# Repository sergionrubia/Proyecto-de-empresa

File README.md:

# sergio
Este va a ser mi repositorio donde voy a guardar todo aquello relacionado con las practicas que estoy haciendo durante mi proyecto de empresa.

Durante este proyecto voy a aprender el funcionamiento del EcoTherm con cada una de sus diferentes partes:
	
	1) Medida Analógica.
	2) Contador (Pulsos).
	3) Medición de temperatura.

De momento en los proyectos subidos a fecha 8 de abril de 2022 están subidos las practicas de de cada una de las partes del EcoTherm y además la primera prática que hice con arduino que consiste en el encendido de varios led con una secuencia programada.

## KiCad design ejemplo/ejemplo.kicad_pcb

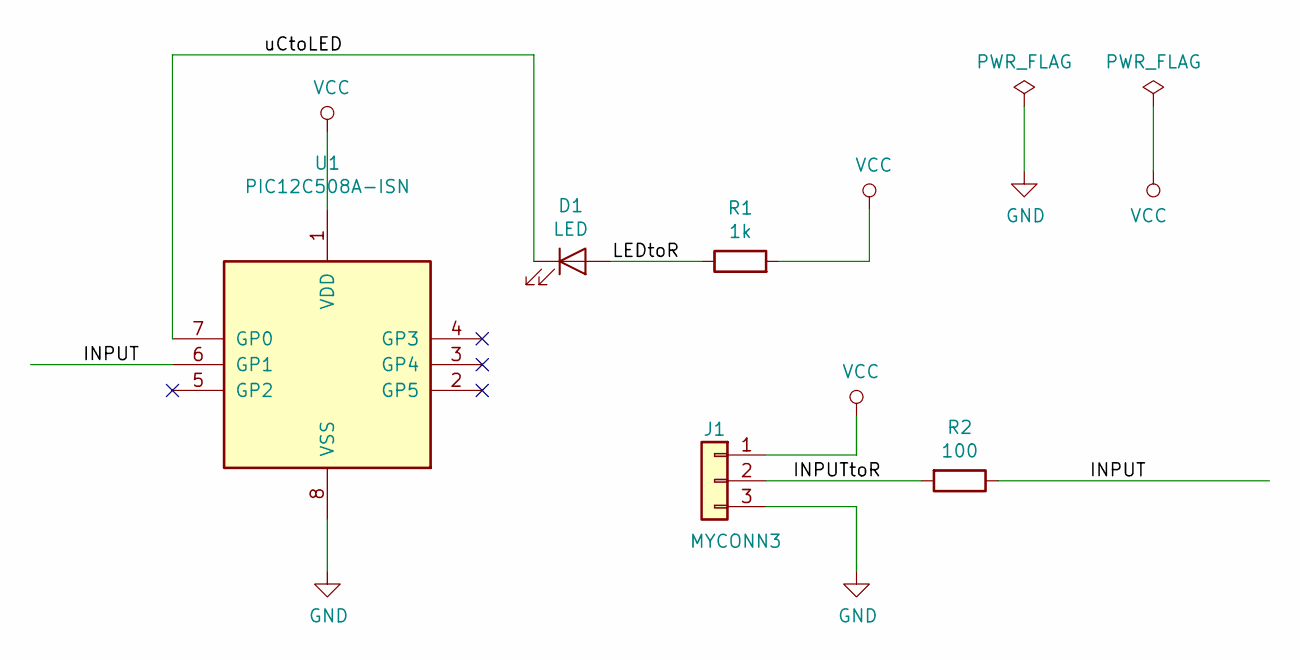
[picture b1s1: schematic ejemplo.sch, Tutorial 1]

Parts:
D1: LED; LED_D5.0mm
J1: MYCONN3; Banana_Jack_3Pin
R1: 1k; R_Axial_DIN0204_L3.6mm_D1.6mm_P1.90mm_Vertical
R2: 100; R_Axial_DIN0204_L3.6mm_D1.6mm_P1.90mm_Vertical
U1: PIC12C508A-ISN; DIP-8_W7.62mm

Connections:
/INPUT: R2.1, U1.6 (GP1)
/INPUTtoR: J1.2, R2.2
/LEDtoR: D1.2 (A), R1.1
/uCtoLED: D1.1 (K), U1.7 (GP0)
GND: J1.3, U1.8 (VSS)
VCC: J1.1, R1.2, U1.1 (VDD)

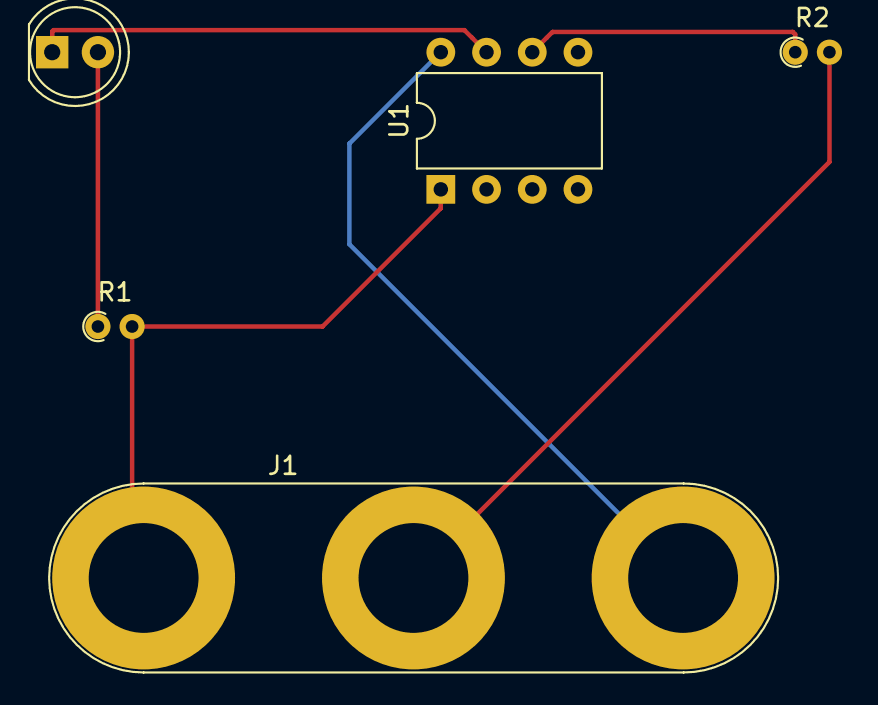
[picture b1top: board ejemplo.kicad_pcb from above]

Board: 2 copper layers, 5 parts (0 on the bottom side), 6 nets.

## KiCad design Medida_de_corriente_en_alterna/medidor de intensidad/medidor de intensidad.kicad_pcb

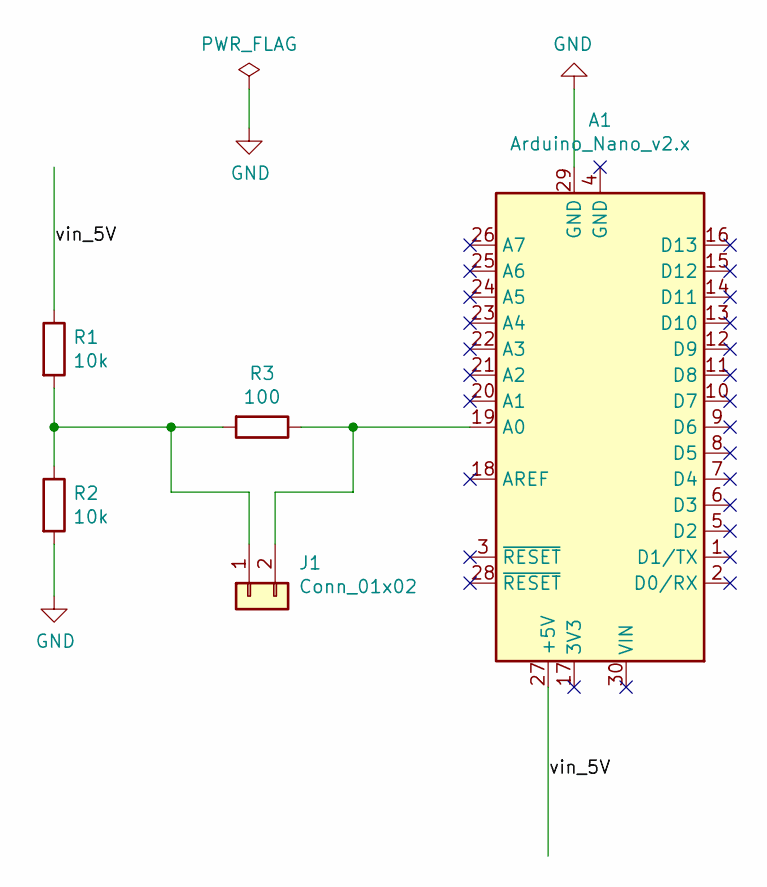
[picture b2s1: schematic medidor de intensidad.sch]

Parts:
A1: Arduino_Nano_v2.x; Arduino_Nano
J1: Conn_01x02; JWT_A3963_1x02_P3.96mm_Vertical
R1, R2: 10k; R_0603_1608Metric
R3: 100; R_0603_1608Metric

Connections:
/vin_5V: A1.27 (+5V), R1.1
GND: A1.29 (GND), R2.2
unnamed: A1.19 (A0), J1.2, R3.1
unnamed: J1.1, R1.2, R2.1, R3.2

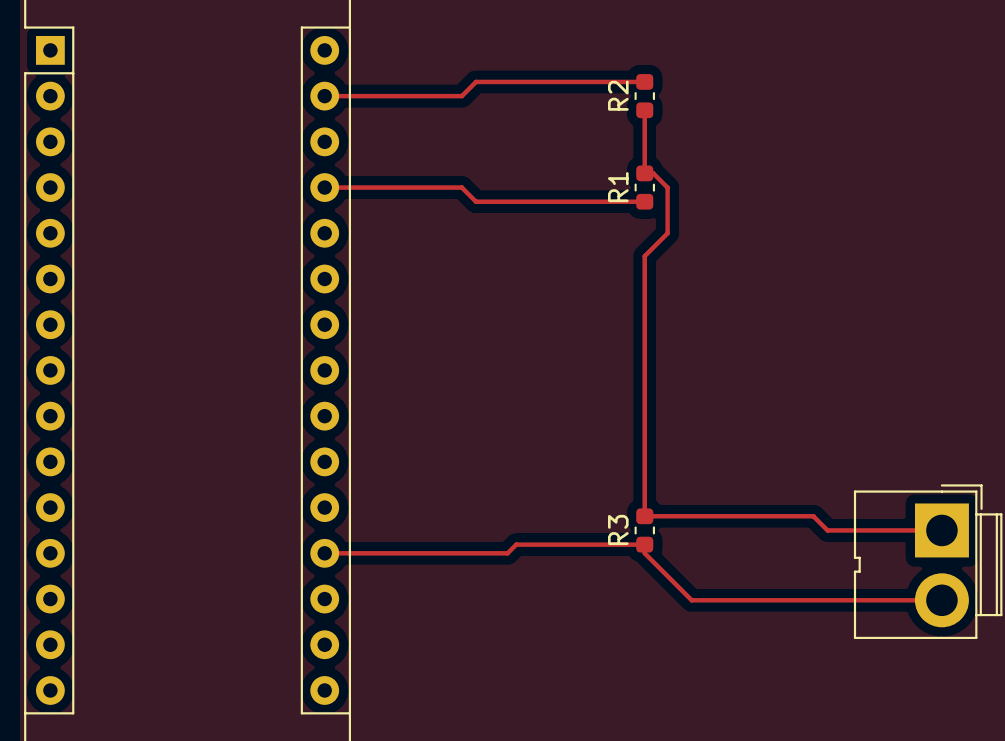
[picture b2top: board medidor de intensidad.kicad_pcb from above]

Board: 2 copper layers, 5 parts (0 on the bottom side), 4 nets.

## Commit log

2022-04-06 segundo commit
2022-04-07 Contador de pulsos
2022-04-07 he creado el codigo del medidor de temperaturas
2022-04-07 modificado el codigo del medidor de temperatura
2022-04-07 eliminado codigo
2022-04-07 añadido el codigo de 3sensores de temperatura
2022-04-08 He cambiado el readme
2022-04-08 Añadido el programa de medida analogica
2022-04-08 Alargado del readme
2022-04-20 Añadido el programa de medida de corriente alterna
2022-04-20 Modificado el programa de medida de corriente alterna
2022-04-21 Añadido el ejemplo de kicad
2022-04-26 Actualización general
2022-04-26 Actualización del codigo de alterna
2022-04-28 Actualización del codigo de alterna2
